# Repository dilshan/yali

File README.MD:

Yet another LCD Interface
=========================

The goal of the YALI (*Yet Another LCD Interface*) project is to provide a universal interface to drive the popular [Hitachi HD44780](https://en.wikipedia.org/wiki/Hitachi_HD44780_LCD_controller) LCD controller. This project offers open hardware module and C/C++ library for the HD44780 controller.

The hardware module of this project consists of a few CMOS logic ICs and a DC boost converter. This module designs to work with 5V and 3.3V DC power sources and logic circuits.

The YALI library is developed using C and is designed to be easily integrated with any C/C++ embedded toolchain. The current version of the YALI library provides built-in interfaces for the following embedded toolchains and platforms:

 - [Arduino](https://www.arduino.cc)
 - [STM32 with LibOpenCM3](https://github.com/libopencm3)
 - [ESP8266 RTOS SDK](https://github.com/espressif/ESP8266_RTOS_SDK)
 - [Mid-range PIC MCUs with MPLAB XC8](https://www.microchip.com/en-us/tools-resources/develop/mplab-xc-compilers)
 
The PCB of the YALI module can also [order from the PCBWay](https://www.pcbway.com/project/shareproject/Universal_HD44780_LCD_interface_e3f2df0c.html) website.

YALI is an open-source project. All the hardware designs and software source codes are available in the YALI project repository. Assembling and interfacing guide for YALI hardware module is also available in [YouTube video](https://youtu.be/gdLx3jKWsBA).

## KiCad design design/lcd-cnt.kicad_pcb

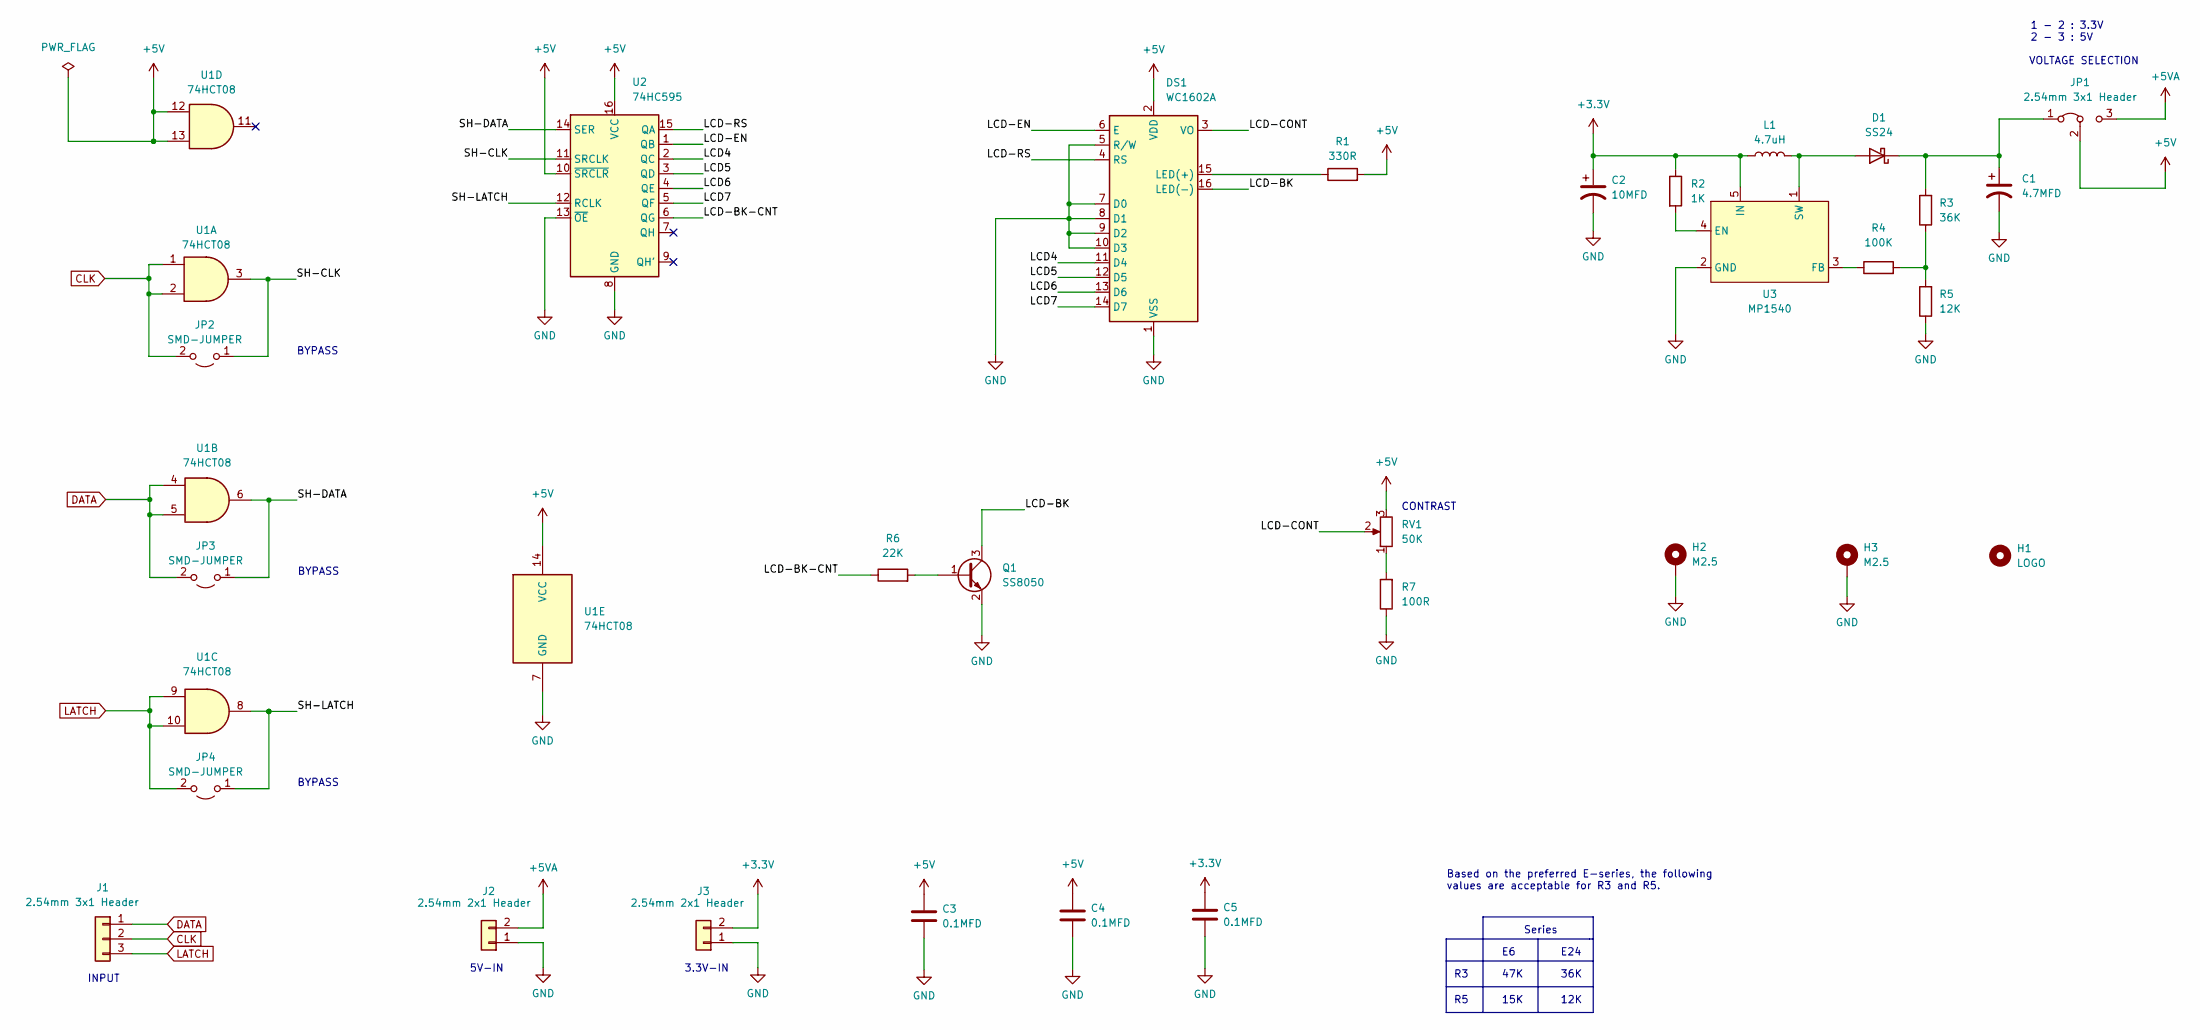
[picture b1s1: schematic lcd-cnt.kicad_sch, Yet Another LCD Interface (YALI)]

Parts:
C1: 4.7MFD; CP_Elec_4x5.8
C2: 10MFD; CP_Elec_5x5.4
C3, C4, C5: 0.1MFD; C_0603_1608Metric_Pad1.08x0.95mm_HandSolder
D1: SS24; D_SMB
DS1: WC1602A
H1: LOGO; pcbway-logo-6mm
H2, H3: M2.5; MountingHole_2.5mm_Pad
J1: 2.54mm 3x1 Header; PinHeader_1x03_P2.54mm_Vertical
J2, J3: 2.54mm 2x1 Header; PinHeader_1x02_P2.54mm_Vertical
JP1: 2.54mm 3x1 Header; PinHeader_1x03_P2.54mm_Vertical
JP2, JP3, JP4: SMD-JUMPER; SolderJumper-2_P1.3mm_Open_TrianglePad1.0x1.5mm
L1: 4.7uH; L_Taiyo-Yuden_NR-60xx_HandSoldering
Q1: SS8050; SOT-23
R1: 330R; R_0603_1608Metric_Pad0.98x0.95mm_HandSolder
R2: 1K; R_0603_1608Metric_Pad0.98x0.95mm_HandSolder
R3: 36K; R_0603_1608Metric_Pad0.98x0.95mm_HandSolder
R4: 100K; R_0603_1608Metric_Pad0.98x0.95mm_HandSolder
R5: 12K; R_0603_1608Metric_Pad0.98x0.95mm_HandSolder
R6: 22K; R_0603_1608Metric_Pad0.98x0.95mm_HandSolder
R7: 100R; R_0603_1608Metric_Pad0.98x0.95mm_HandSolder
RV1: 50K; Potentiometer_Runtron_RM-065_Vertical
U1: 74HCT08; SO-14_3.9x8.65mm_P1.27mm
U2: 74HC595; SO-16_3.9x9.9mm_P1.27mm
U3: MP1540; TSOT-23-5

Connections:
+3.3V: C2.1, C5.1, J3.2, L1.1, R2.1, U3.5 (IN)
+5V: C3.1, C4.1, DS1.2 (VDD), JP1.2 (C), R1.2, RV1.3, U1.12, U1.13, U1.14 (VCC), U2.10 (~SRCLR), U2.16 (VCC)
+5VA: J2.2, JP1.3 (B)
/LCD4: DS1.11 (D4), U2.2 (QC)
/LCD5: DS1.12 (D5), U2.3 (QD)
/LCD6: DS1.13 (D6), U2.4 (QE)
/LCD7: DS1.14 (D7), U2.5 (QF)
/LCD-BK: DS1.16 (LED(-)), Q1.3 (C)
/LCD-BK-CNT: R6.1, U2.6 (QG)
/LCD-CONT: DS1.3 (VO), RV1.2
/LCD-EN: DS1.6 (E), U2.1 (QB)
/LCD-RS: DS1.4 (RS), U2.15 (QA)
/SH-CLK: JP2.1 (A), U1.3, U2.11 (SRCLK)
/SH-DATA: JP3.1 (A), U1.6, U2.14 (SER)
/SH-LATCH: JP4.1 (A), U1.8, U2.12 (RCLK)
CLK: J1.2, JP2.2 (B), U1.1, U1.2
DATA: J1.1, JP3.2 (B), U1.4, U1.5
GND: C1.2, C2.2, C3.2, C4.2, C5.2, DS1.1 (VSS), DS1.5 (R/W), DS1.7 (D0), DS1.8 (D1), DS1.9 (D2), DS1.10 (D3), H2.1, H3.1, J2.1, J3.1, Q1.2 (E), R5.1, R7.1, U1.7 (GND), U2.8 (GND), U2.13 (~OE), U3.2 (GND)
LATCH: J1.3, JP4.2 (B), U1.9, U1.10
unnamed: C1.1, D1.1 (K), JP1.1 (A), R3.2
unnamed: D1.2 (A), L1.2, U3.1 (SW)
unnamed: DS1.15 (LED(+)), R1.1
unnamed: Q1.1 (B), R6.2
unnamed: R2.2, U3.4 (EN)
unnamed: R3.1, R4.2, R5.2
unnamed: R4.1, U3.3 (FB)
unnamed: R7.2, RV1.1

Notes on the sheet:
BYPASS
CONTRAST
INPUT
15K
47K
1 - 2 : 3.3V 2 - 3 : 5V
Based on the preferred E-series, the following values are acceptable for R3 and R5.
12K
3.3V-IN
E24
VOLTAGE SELECTION
5V-IN
36K
Series

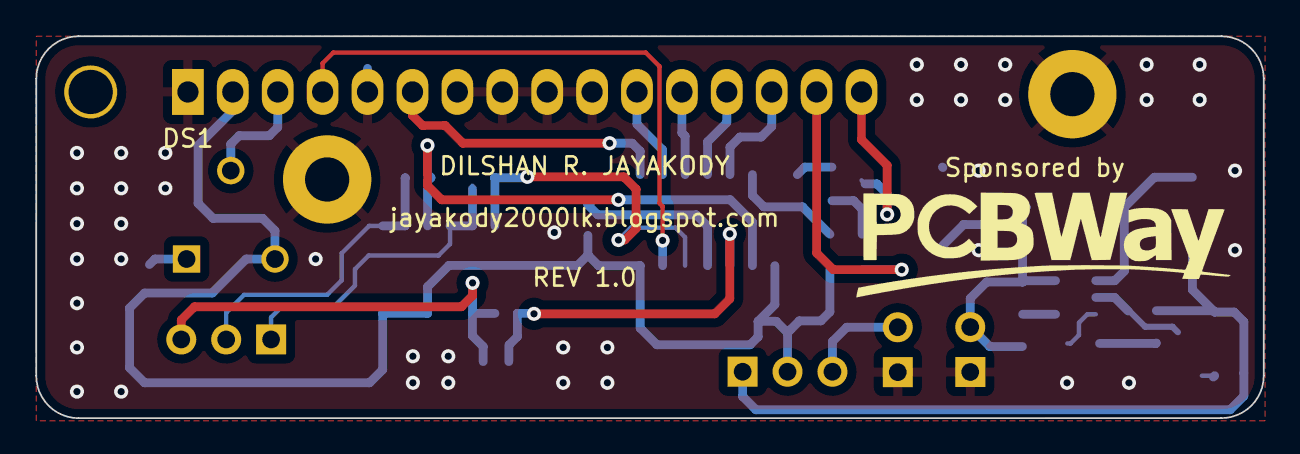
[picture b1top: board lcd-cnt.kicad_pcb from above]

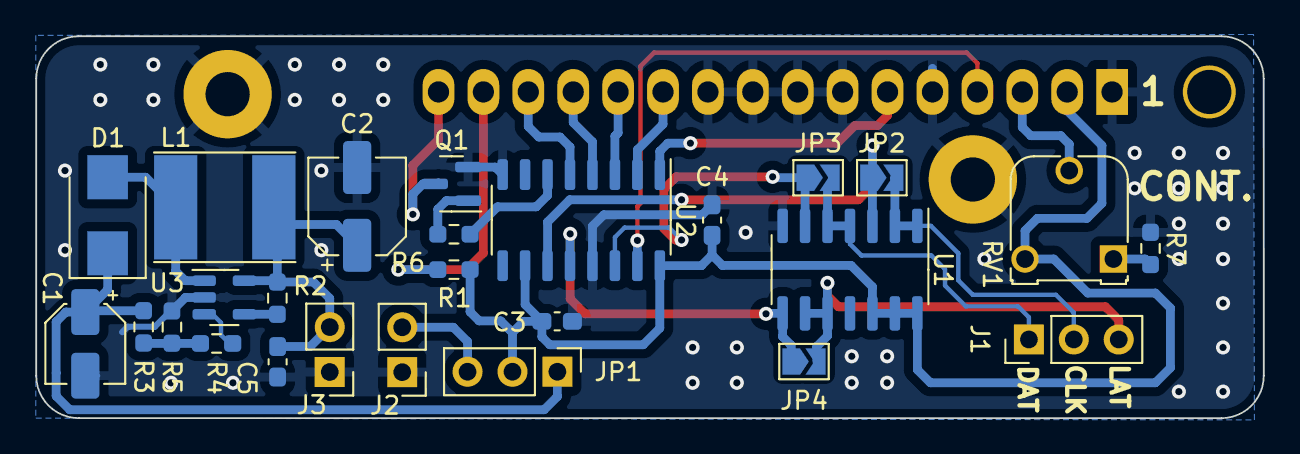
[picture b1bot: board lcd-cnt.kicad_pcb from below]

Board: 2 copper layers, 69.4 x 21.6 mm, 30 parts (26 on the bottom side), 27 nets.

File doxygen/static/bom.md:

Bill of Materials
=================

| Designator | Component                        | Package                  | Quantity | Datasheet                                                                            |
|------------|----------------------------------|--------------------------|----------|--------------------------------------------------------------------------------------|
| C1         | 4.7µF / 10V                      | SMD Electrolytic 4 x 5.8 | 1        |                                                                                      |
| C2         | 10µF / 10V                       | SMD Electrolytic 5 x 5.4 | 1        |                                                                                      |
| C3, C4, C5 | 0.1µF / 25V                      | SMD 0603                 | 3        |                                                                                      |
| R1         | 330Ω                             | SMD 0603                 | 1        |                                                                                      |
| R2         | 1KΩ                              | SMD 0603                 | 1        |                                                                                      |
| R3         | 36KΩ                             | SMD 0603                 | 1        |                                                                                      |
| R4         | 100KΩ                            | SMD 0603                 | 1        |                                                                                      |
| R5         | 12KΩ                             | SMD 0603                 | 1        |                                                                                      |
| R6         | 22KΩ                             | SMD 0603                 | 1        |                                                                                      |
| R7         | 100Ω                             | SMD 0603                 | 1        |                                                                                      |
| D1         | SS24                             | SMD SMB                  | 1        | https://www.onsemi.com/pdf/datasheet/ss24-d.pdf                                      |
| L1         | 4.7µH                            | SMD Inductor             | 1        |                                                                                      |
| RV1        | 50KΩ                             | THT RM65                 | 1        |                                                                                      |
| J1, JP1    | 2.54mm – 3x1-pin male pin header | THT                      | 2        |                                                                                      |
| J2, J3     | 2.54mm – 2x1-pin male pin header | THT                      | 2        |                                                                                      |
| DS1        | 2.54mm – 16x-pin female header   | THT                      | 1        |                                                                                      |
| U1         | 74HCT08                          | SMD SO-14                | 1        | https://www.diodes.com/assets/Datasheets/74HCT08.pdf                                 |
| U2         | 74HC595                          | SMD SO-16                | 1        | https://www.diodes.com/assets/Datasheets/74HC595.pdf                                 |
| U3         | MP1540                           | SMD SOT-23-5             | 1        | http://www1.futureelectronics.com/doc/MONOLITHIC%20POWER%20S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 |
| Q1         | SS8050                           | SMD SOT-23               | 1        | https://www.onsemi.com/pdf/datasheet/ss8050-d.pdf                                    |

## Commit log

2023-03-23 Initial version of firmware for Arduino and MPLAB XC.
2023-03-23 Update version and license block of demo files.
2023-03-24 Initial version of schematic and PCB design.
2023-03-24 Add initial version of STM32 support with LibOpenCM3.
2023-03-24 File cleanup and remove VSCODE directory.
2023-03-25 Add initial version of ESP8266 support.
2023-03-25 Add initial version of API documentation.
2023-03-25 Revert "Add initial version of API documentation."
    This reverts commit ee39a17c0c905787d0dca363753949715494f772.
2023-03-26 Update readme file and upload image of the YALI module.
2023-03-27 Add API documentation and integration guides.
2023-03-28 Add purchase links to the BOM.
2023-03-28 Add YouTube video link
2023-03-28 Update readme with YouTube video link.
2023-03-28 Change directory structure of the /doc.
2023-03-28 Update main page of the documentation with YouTube video link.
2023-03-30 Add PCBWay purchase link.
